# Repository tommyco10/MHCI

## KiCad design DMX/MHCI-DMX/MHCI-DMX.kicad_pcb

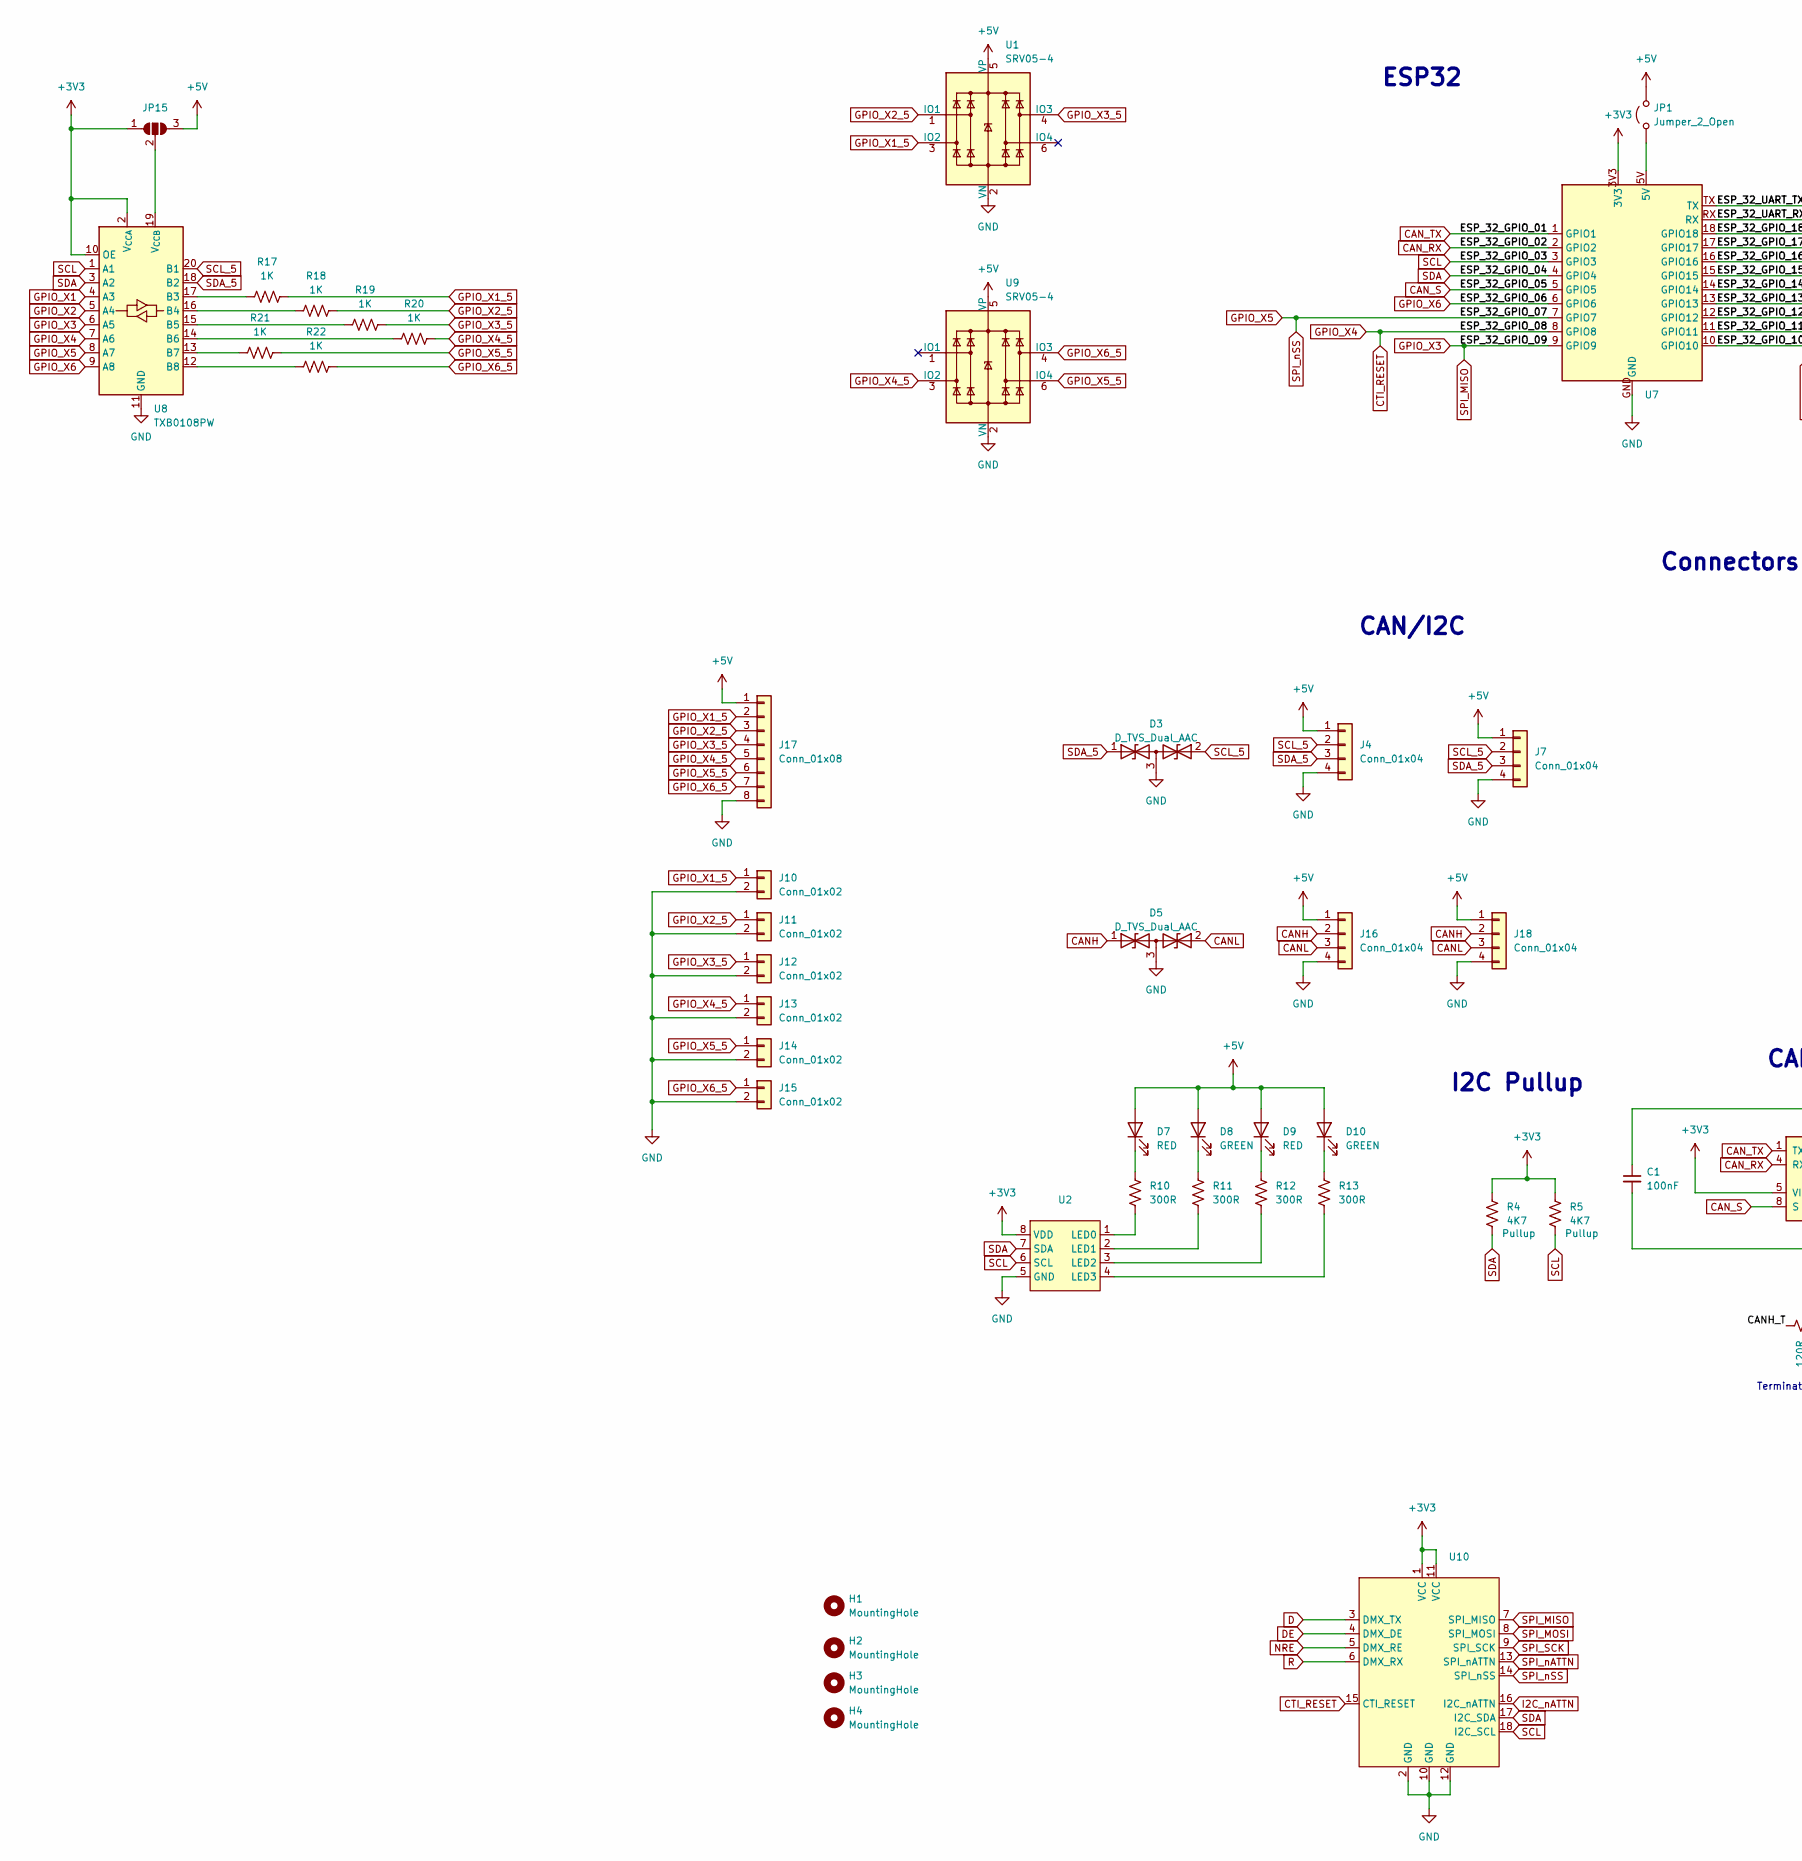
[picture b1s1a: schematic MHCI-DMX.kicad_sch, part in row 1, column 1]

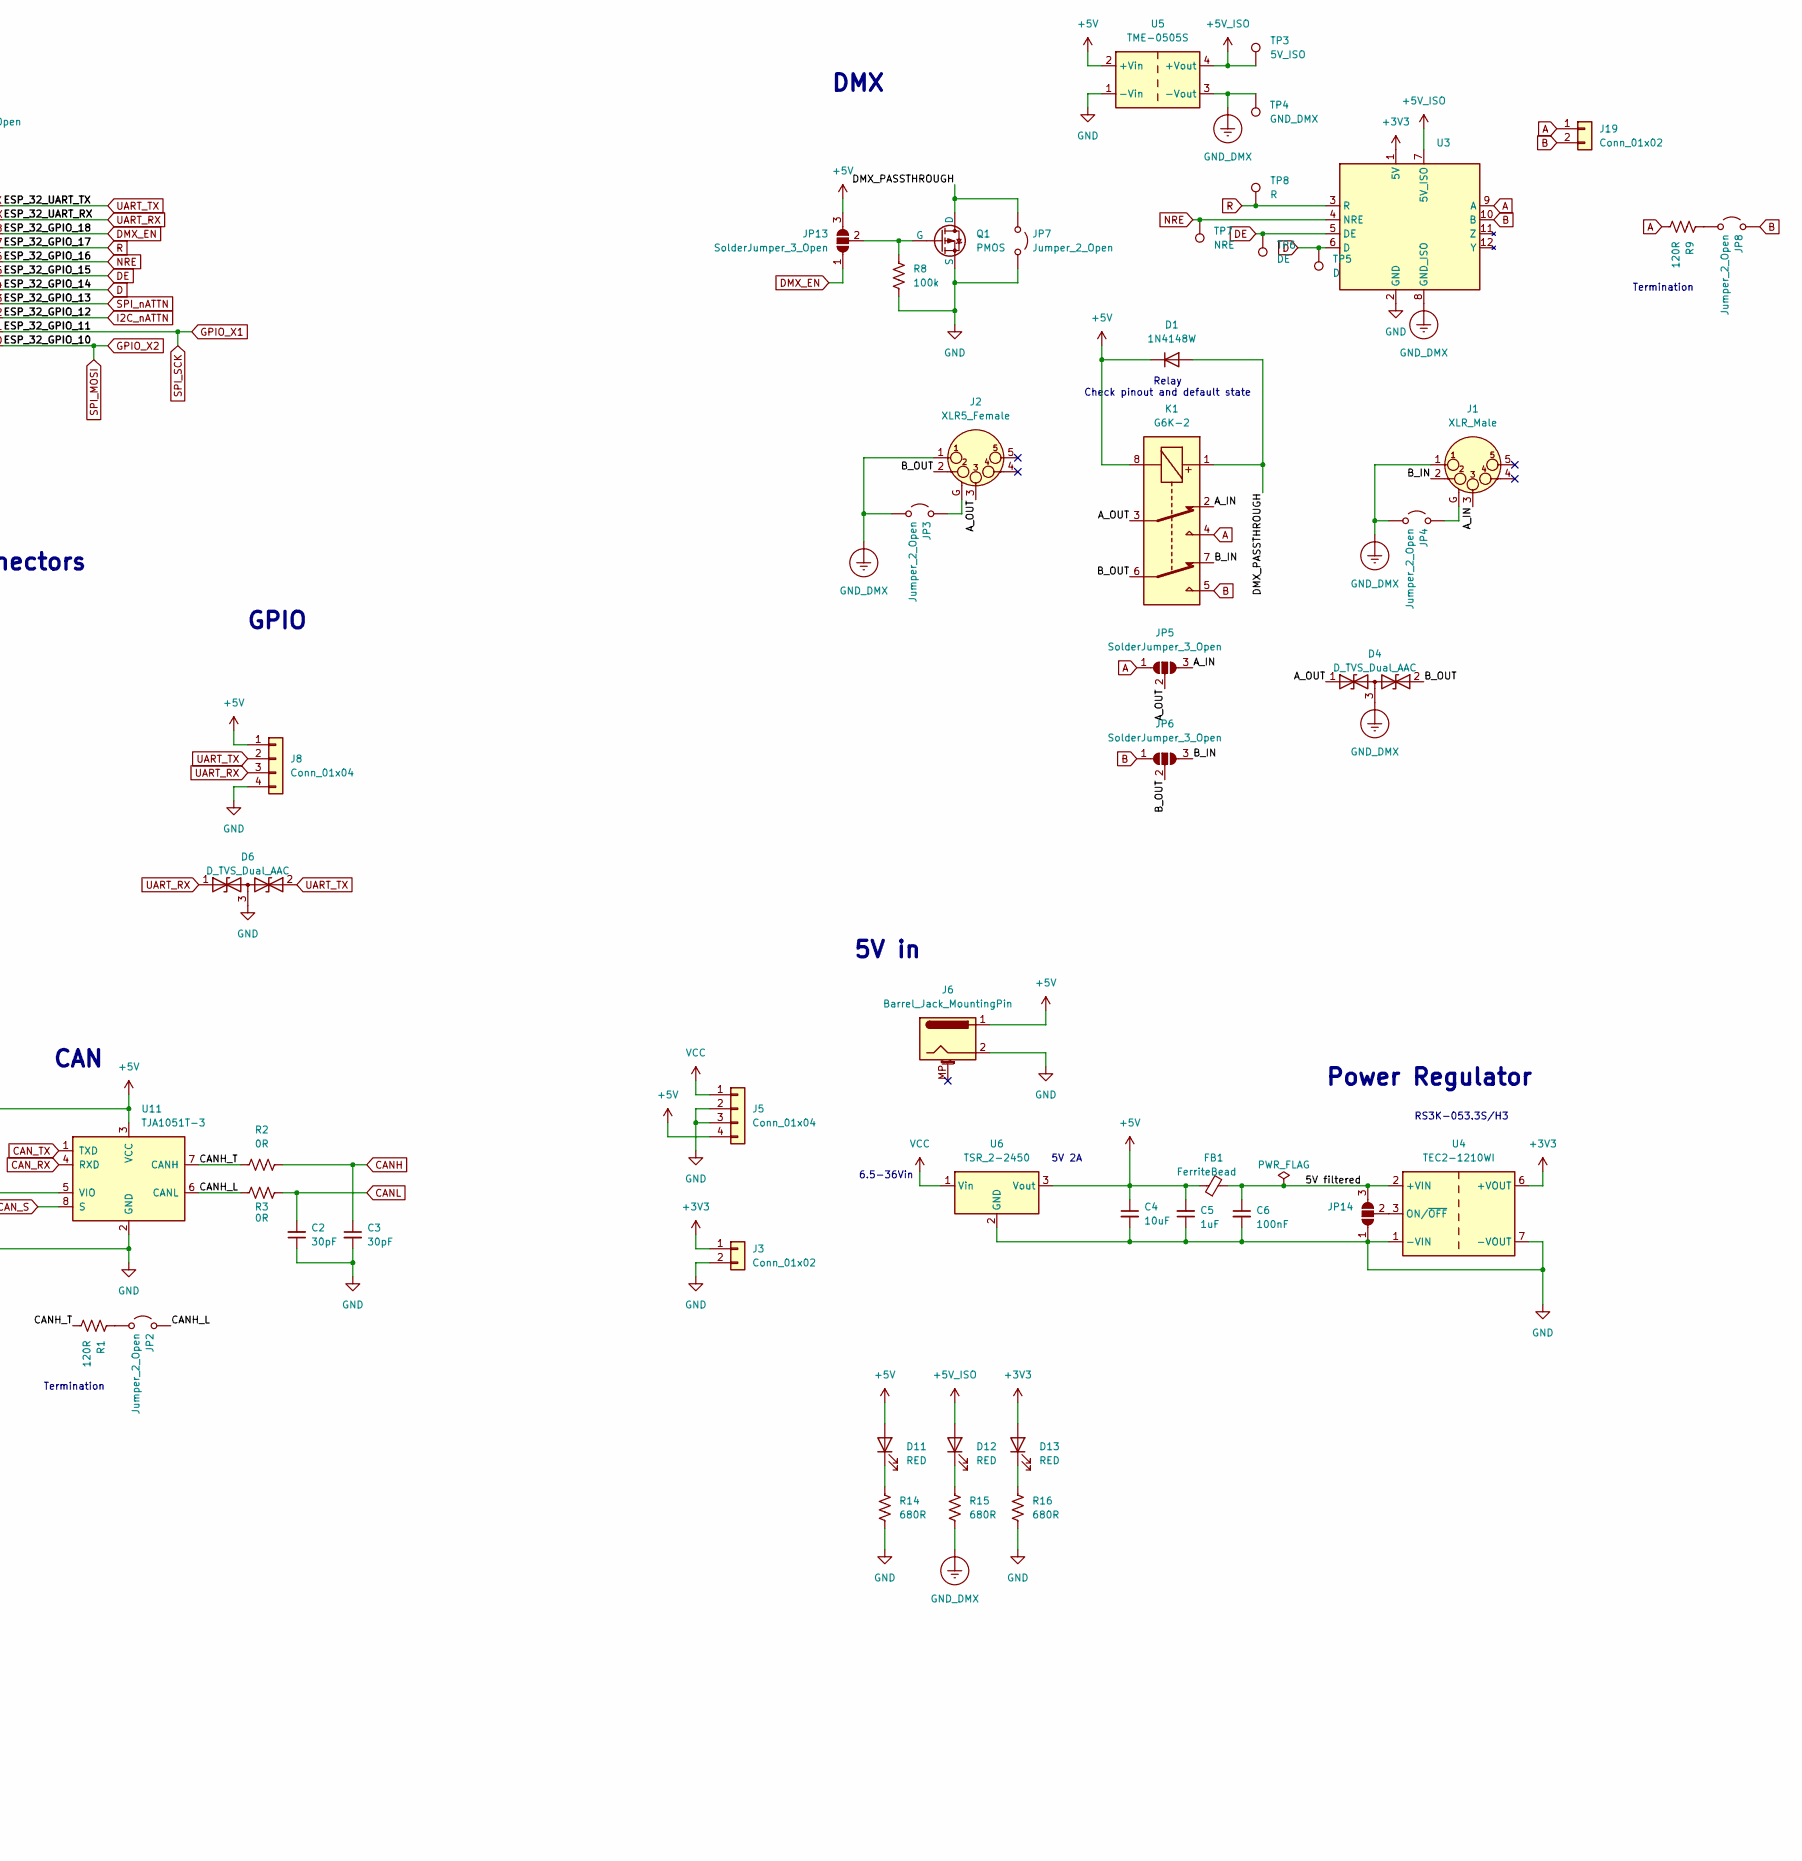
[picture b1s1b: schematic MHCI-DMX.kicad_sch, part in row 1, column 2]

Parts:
C1, C6: 100nF; C_0402_1005Metric; LCSC C1525
C2, C3: 30pF; C_0402_1005Metric; LCSC C1570
C4: 10uF; C_0603_1608Metric; LCSC C96446
C5: 1uF; C_0402_1005Metric; LCSC C52923
D1: 1N4148W; D_SOD-123; LCSC C2099
D3, D4, D5, D6: D_TVS_Dual_AAC; SOT-23; LCSC C32677
D7, D9, D11, D12, D13: RED; LED_0603_1608Metric; LCSC C2286
D8, D10: GREEN; LED_0603_1608Metric
FB1: FerriteBead; D_0805_2012Metric; LCSC C1015
H1, H2, H3, H4: MountingHole; MountingHole_3.2mm_M3
J1: XLR_Male; Jack_XLR_Neutrik_NC5MAH_LR
J2: XLR5_Female; Jack_XLR_Neutrik_NC5FAH_LR-DAE
J3, J19: Conn_01x02; PinHeader_1x02_P2.54mm_Vertical
J4, J7, J8, J16, J18: Conn_01x04; PinSocket_1x04_P2.54mm_Vertical
J5: Conn_01x04; PinHeader_1x04_P2.54mm_Vertical
J6: Barrel_Jack_MountingPin; BarrelJack_GCT_DCJ200-10-A_Horizontal
J10, J11, J12, J13, J14, J15: Conn_01x02; 2060-452-998-404 Wago
J17: Conn_01x08; PinSocket_1x08_P2.54mm_Vertical
JP1, JP2, JP3, JP4, JP7, JP8: Jumper_2_Open; SolderJumper-2_P1.3mm_Open_RoundedPad1.0x1.5mm
JP5, JP6, JP13, JP14, JP15: SolderJumper_3_Open; SolderJumper-3_P1.3mm_Open_RoundedPad1.0x1.5mm
K1: G6K-2; Relay_DPDT_Omron_G6K-2F
Q1: PMOS; SOT-23; LCSC C10487
R1, R9: 120R; R_0402_1005Metric; LCSC C25079
R2, R3: 0R; R_0402_1005Metric; LCSC C17168
R4, R5: 4K7; R_0603_1608Metric; LCSC C23162
R8: 100k; R_0603_1608Metric; LCSC C25803
R10, R11, R12, R13: 300R; R_0603_1608Metric; LCSC C23025
R14, R15, R16: 680R; R_0603_1608Metric; LCSC C23228
R17, R18, R19, R20, R21, R22: 1K; R_0603_1608Metric; LCSC C21190
TP3: 5V_ISO; TestPoint_Pad_D1.0mm
TP4: GND_DMX; TestPoint_Pad_D1.0mm
TP5: D; TestPoint_Pad_D1.0mm
TP6: DE; TestPoint_Pad_D1.0mm
TP7: NRE; TestPoint_Pad_D1.0mm
TP8: R; TestPoint_Pad_D1.0mm
U1, U9: SRV05-4; SOT-23-6; LCSC C85364
U2: TSSOP-8_3x3mm_P0.65mm; LCSC C88381
U3: ISO-DMX
U4: TEC2-1210WI; Converter_DCDC_TRACO_TMR-xxxx_THT
U5: TME-0505S; Converter_DCDC_TRACO_TME_03xxS_05xxS_12xxS_Single_THT
U6: TSR_2-2450; Converter_DCDC_TRACO_TSR-1_THT
U7: ESP-32-S3-Tiny - PTH
U8: TXB0108PW; TSSOP-20_4.4x6.5mm_P0.65mm
U10: WirelessDMX-Module
U11: TJA1051T-3; SOIC-8_3.9x4.9mm_P1.27mm; LCSC C5342108

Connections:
+3V3: D13.2 (A), J3.1, JP15.1 (A), R4.1, R5.1, U2.8 (VDD), U3.1 (5V), U4.6 (+VOUT), U7.3V3, U8.2 (V_{CCA}), U8.10 (OE), U10.1 (VCC), U10.11 (VCC), U11.5 (VIO)
+5V: C1.1, C4.1, C5.2, D1.1 (K), D7.2 (A), D8.2 (A), D9.2 (A), D10.2 (A), D11.2 (A), FB1.1, J4.1, J5.4, J6.1, J7.1, J8.1, J16.1, J17.1, J18.1, JP1.2 (B), JP13.3 (B), JP15.3 (B), K1.8, U1.5 (VP), U5.2 (+Vin), U6.3 (Vout), U9.5 (VP), U11.3 (VCC)
+5V_ISO: D12.2 (A), TP3.1, U3.7 (5V_ISO), U5.4 (+Vout)
/5V filtered: C6.1, FB1.2, JP14.3 (B), U4.2 (+VIN)
/A_IN: J1.3, JP5.3 (B), K1.2
/A_OUT: D4.1 (A1), J2.3, JP5.2 (C), K1.3
/B_IN: J1.2, JP6.3 (B), K1.7
/B_OUT: D4.2 (A2), J2.2, JP6.2 (C), K1.6
/CANH_L: JP2.2 (B), R3.1, U11.6 (CANL)
/CANH_T: R1.1, R2.2, U11.7 (CANH)
/DMX_PASSTHROUGH: D1.2 (A), JP7.1 (A), K1.1, Q1.3 (D)
A: J19.1, JP5.1 (A), K1.4, R9.1, U3.9 (A)
B: J19.2, JP6.1 (A), JP8.2 (B), K1.5, U3.10 (B)
CANH: C3.1, D5.1 (A1), J16.2, J18.2, R2.1
CANL: C2.2, D5.2 (A2), J16.3, J18.3, R3.2
CAN_RX: U7.2 (GPIO2), U11.4 (RXD)
CAN_S: U7.5 (GPIO5), U11.8 (S)
CAN_TX: U7.1 (GPIO1), U11.1 (TXD)
CTI_RESET: U7.8 (GPIO8), U8.7 (A6), U10.15 (CTI_RESET)
D: TP5.1, U3.6 (D), U7.14 (GPIO14), U10.3 (DMX_TX)
DE: TP6.1, U3.5 (DE), U7.15 (GPIO15), U10.4 (DMX_DE)
DMX_EN: JP13.1 (A), U7.18 (GPIO18)
GND: C1.2, C2.1, C3.2, C4.2, C5.1, C6.2, D3.3 (common), D5.3 (common), D6.3 (common), J3.2, J4.4, J5.2, J5.3, J6.2, J7.4, J8.4, J10.2, J11.2, J12.2, J13.2, J14.2, J15.2, J16.4, J17.8, J18.4, JP7.2 (B), JP14.1 (A), Q1.2 (S), R8.2, R14.2, R16.2, U1.2 (VN), U2.5 (GND), U3.2 (GND), U4.1 (-VIN), U4.7 (-VOUT), U5.1 (-Vin), U6.2 (GND), U7.GND, U8.11 (GND), U9.2 (VN), U10.2 (GND), U10.10 (GND), U10.12 (GND), U11.2 (GND)
GND_DMX: D4.3 (common), J1.1, J2.1, JP3.1 (A), JP4.1 (A), R15.2, TP4.1, U3.8 (GND_ISO), U5.3 (-Vout)
GPIO_X1: U7.11 (GPIO11), U8.4 (A3), U10.9 (SPI_SCK)
GPIO_X1_5: J10.1, J17.2, R17.2, U1.3 (IO2)
GPIO_X2: U7.10 (GPIO10), U8.5 (A4), U10.8 (SPI_MOSI)
GPIO_X2_5: J11.1, J17.3, R18.2, U1.1 (IO1)
GPIO_X3: U7.9 (GPIO9), U8.6 (A5), U10.7 (SPI_MISO)
GPIO_X3_5: J12.1, J17.4, R19.2, U1.4 (IO3)
GPIO_X4_5: J13.1, J17.5, R20.2, U9.3 (IO2)
GPIO_X5: U7.7 (GPIO7), U8.8 (A7), U10.14 (SPI_nSS)
GPIO_X5_5: J14.1, J17.6, R21.2, U9.6 (IO4)
GPIO_X6: U7.6 (GPIO6), U8.9 (A8)
GPIO_X6_5: J15.1, J17.7, R22.2, U9.4 (IO3)
I2C_nATTN: U7.12 (GPIO12), U10.16 (I2C_nATTN)
NRE: TP7.1, U3.4 (NRE), U7.16 (GPIO16), U10.5 (DMX_RE)
unnamed: D7.1 (K), R10.1
unnamed: D8.1 (K), R11.1
unnamed: D9.1 (K), R12.1
unnamed: D10.1 (K), R13.1
unnamed: D11.1 (K), R14.1
unnamed: D12.1 (K), R15.1
unnamed: D13.1 (K), R16.1
unnamed: JP1.1 (A), U7.5V
unnamed: JP2.1 (A), R1.2
unnamed: J2.G, JP3.2 (B)
unnamed: J1.G, JP4.2 (B)
unnamed: JP8.1 (A), R9.2
unnamed: JP13.2 (C), Q1.1 (G), R8.1
unnamed: JP14.2 (C), U4.3 (ON/~OFF)
unnamed: JP15.2 (C), U8.19 (V_{CCB})
unnamed: R10.2, U2.1 (LED0)
unnamed: R11.2, U2.2 (LED1)
unnamed: R12.2, U2.3 (LED2)
unnamed: R13.2, U2.4 (LED3)
unnamed: R17.1, U8.17 (B3)
unnamed: R18.1, U8.16 (B4)
unnamed: R19.1, U8.15 (B5)
unnamed: R20.1, U8.14 (B6)
unnamed: R21.1, U8.13 (B7)
unnamed: R22.1, U8.12 (B8)
R: TP8.1, U3.3 (R), U7.17 (GPIO17), U10.6 (DMX_RX)
SCL: R5.2, U2.6 (SCL), U7.3 (GPIO3), U8.1 (A1), U10.18 (I2C_SCL)
SCL_5: D3.2 (A2), J4.2, J7.2, U8.20 (B1)
SDA: R4.2, U2.7 (SDA), U7.4 (GPIO4), U8.3 (A2), U10.17 (I2C_SDA)
SDA_5: D3.1 (A1), J4.3, J7.3, U8.18 (B2)
SPI_nATTN: U7.13 (GPIO13), U10.13 (SPI_nATTN)
UART_RX: D6.1 (A1), J8.3, U7.RX
UART_TX: D6.2 (A2), J8.2, U7.TX
VCC: J5.1, U6.1 (Vin)

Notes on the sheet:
Connectors
5V 2A
CAN
DMX
Termination
RS3K-053.3S/H3
5V in
Relay Check pinout and default state
ESP32
CAN/I2C
I2C Pullup
GPIO
Power Regulator
6.5-36Vin

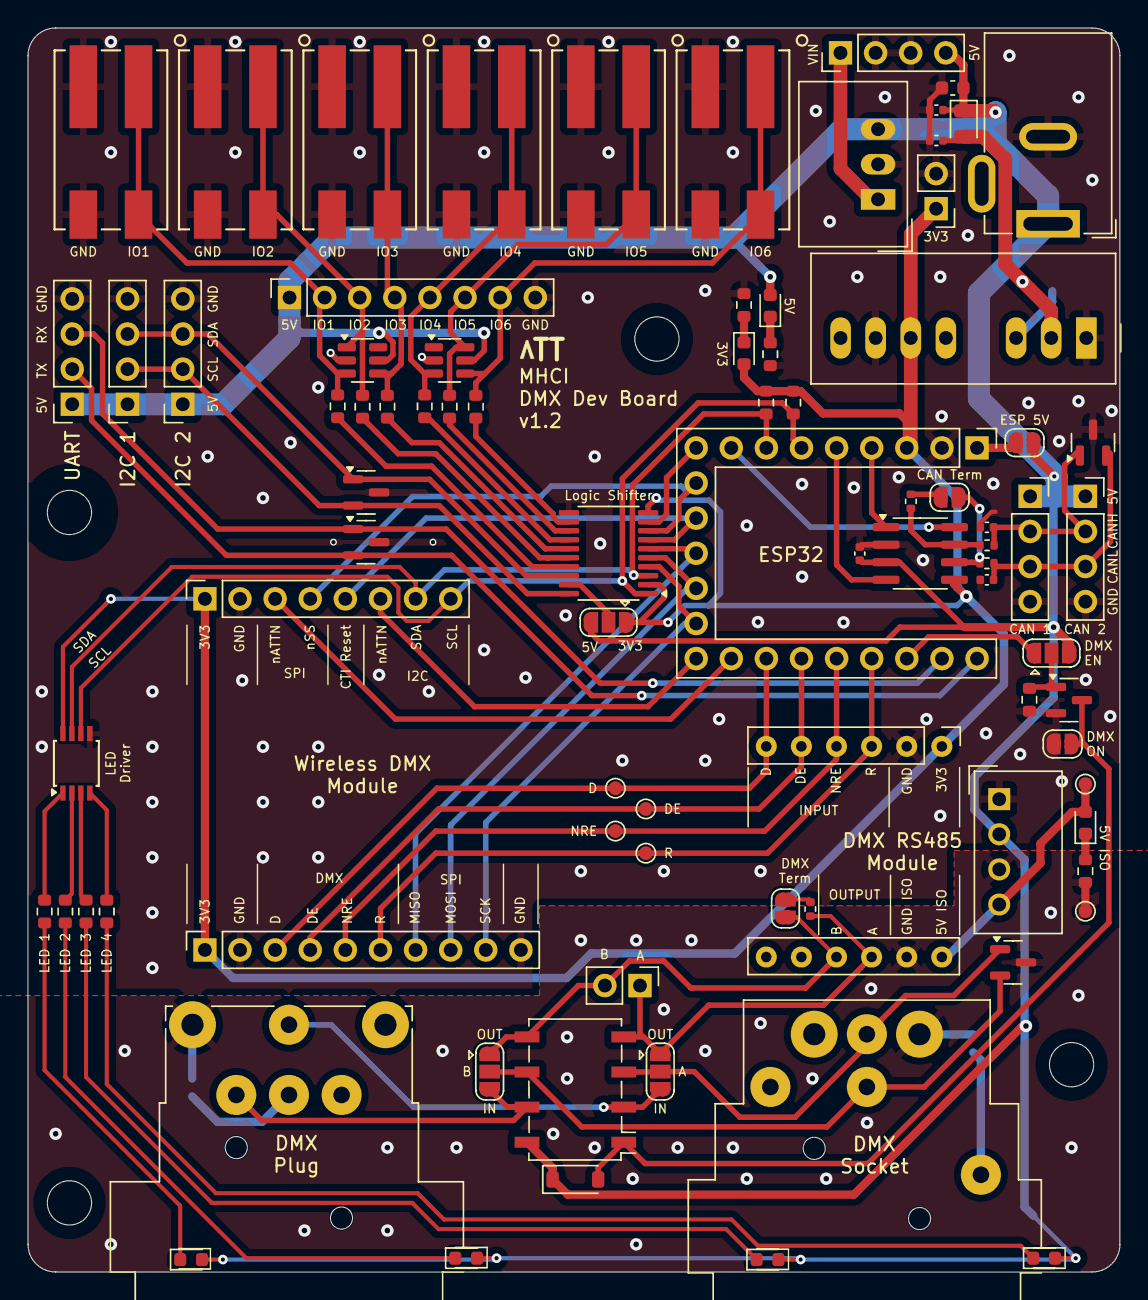
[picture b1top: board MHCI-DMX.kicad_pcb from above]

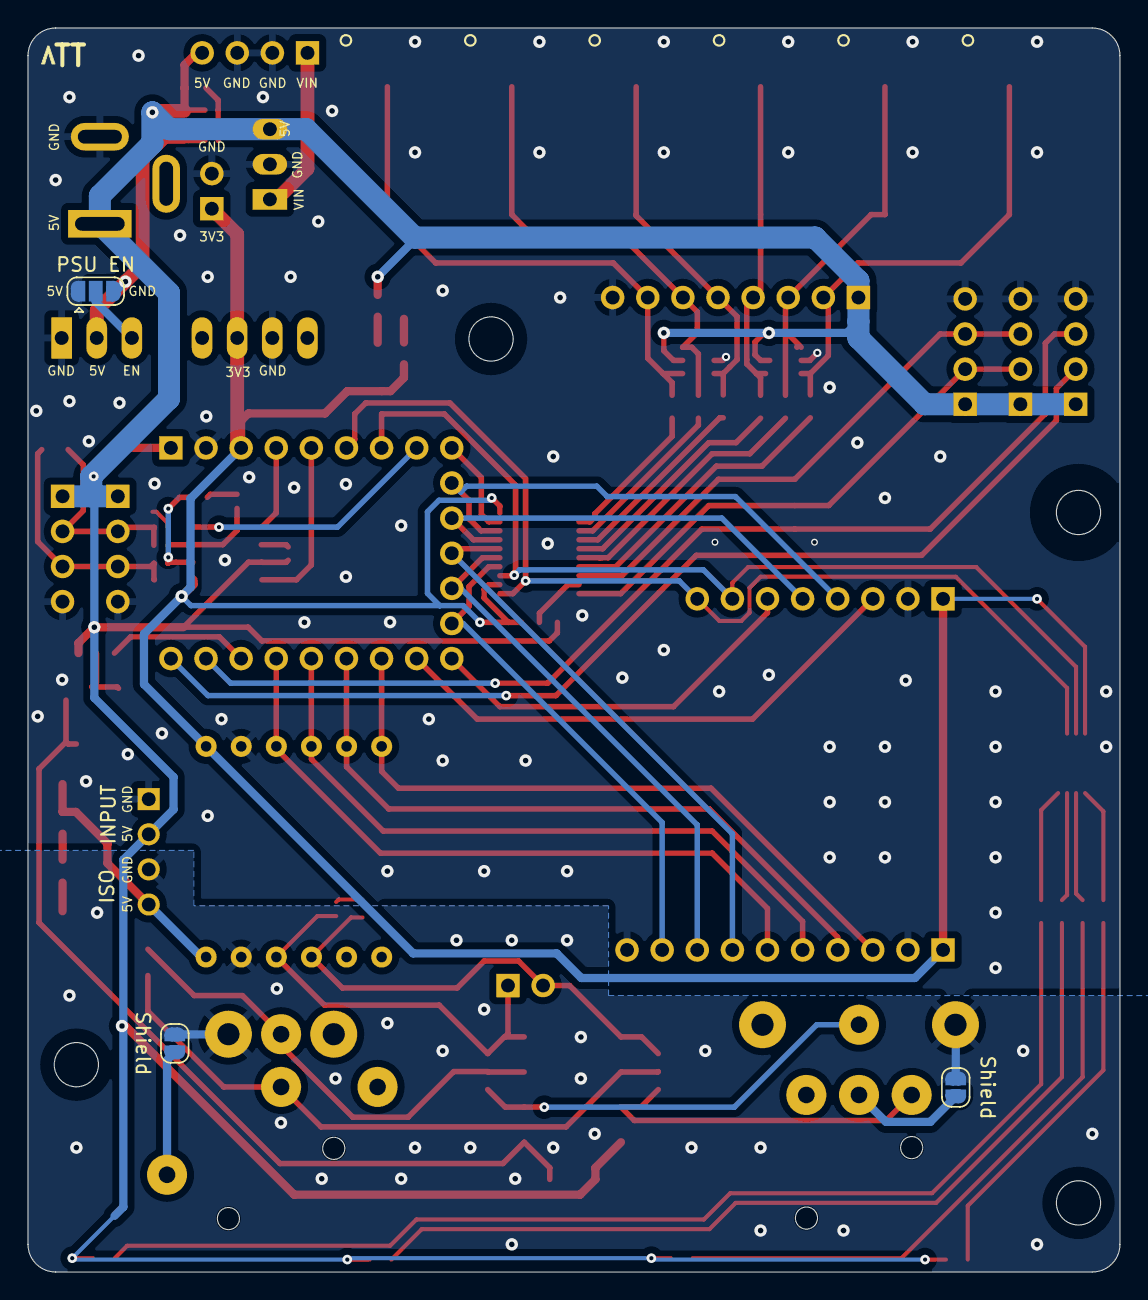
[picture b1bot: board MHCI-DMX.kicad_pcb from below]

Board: 2 copper layers, 79.0 x 90.0 mm, 91 parts (3 on the bottom side), 71 nets.

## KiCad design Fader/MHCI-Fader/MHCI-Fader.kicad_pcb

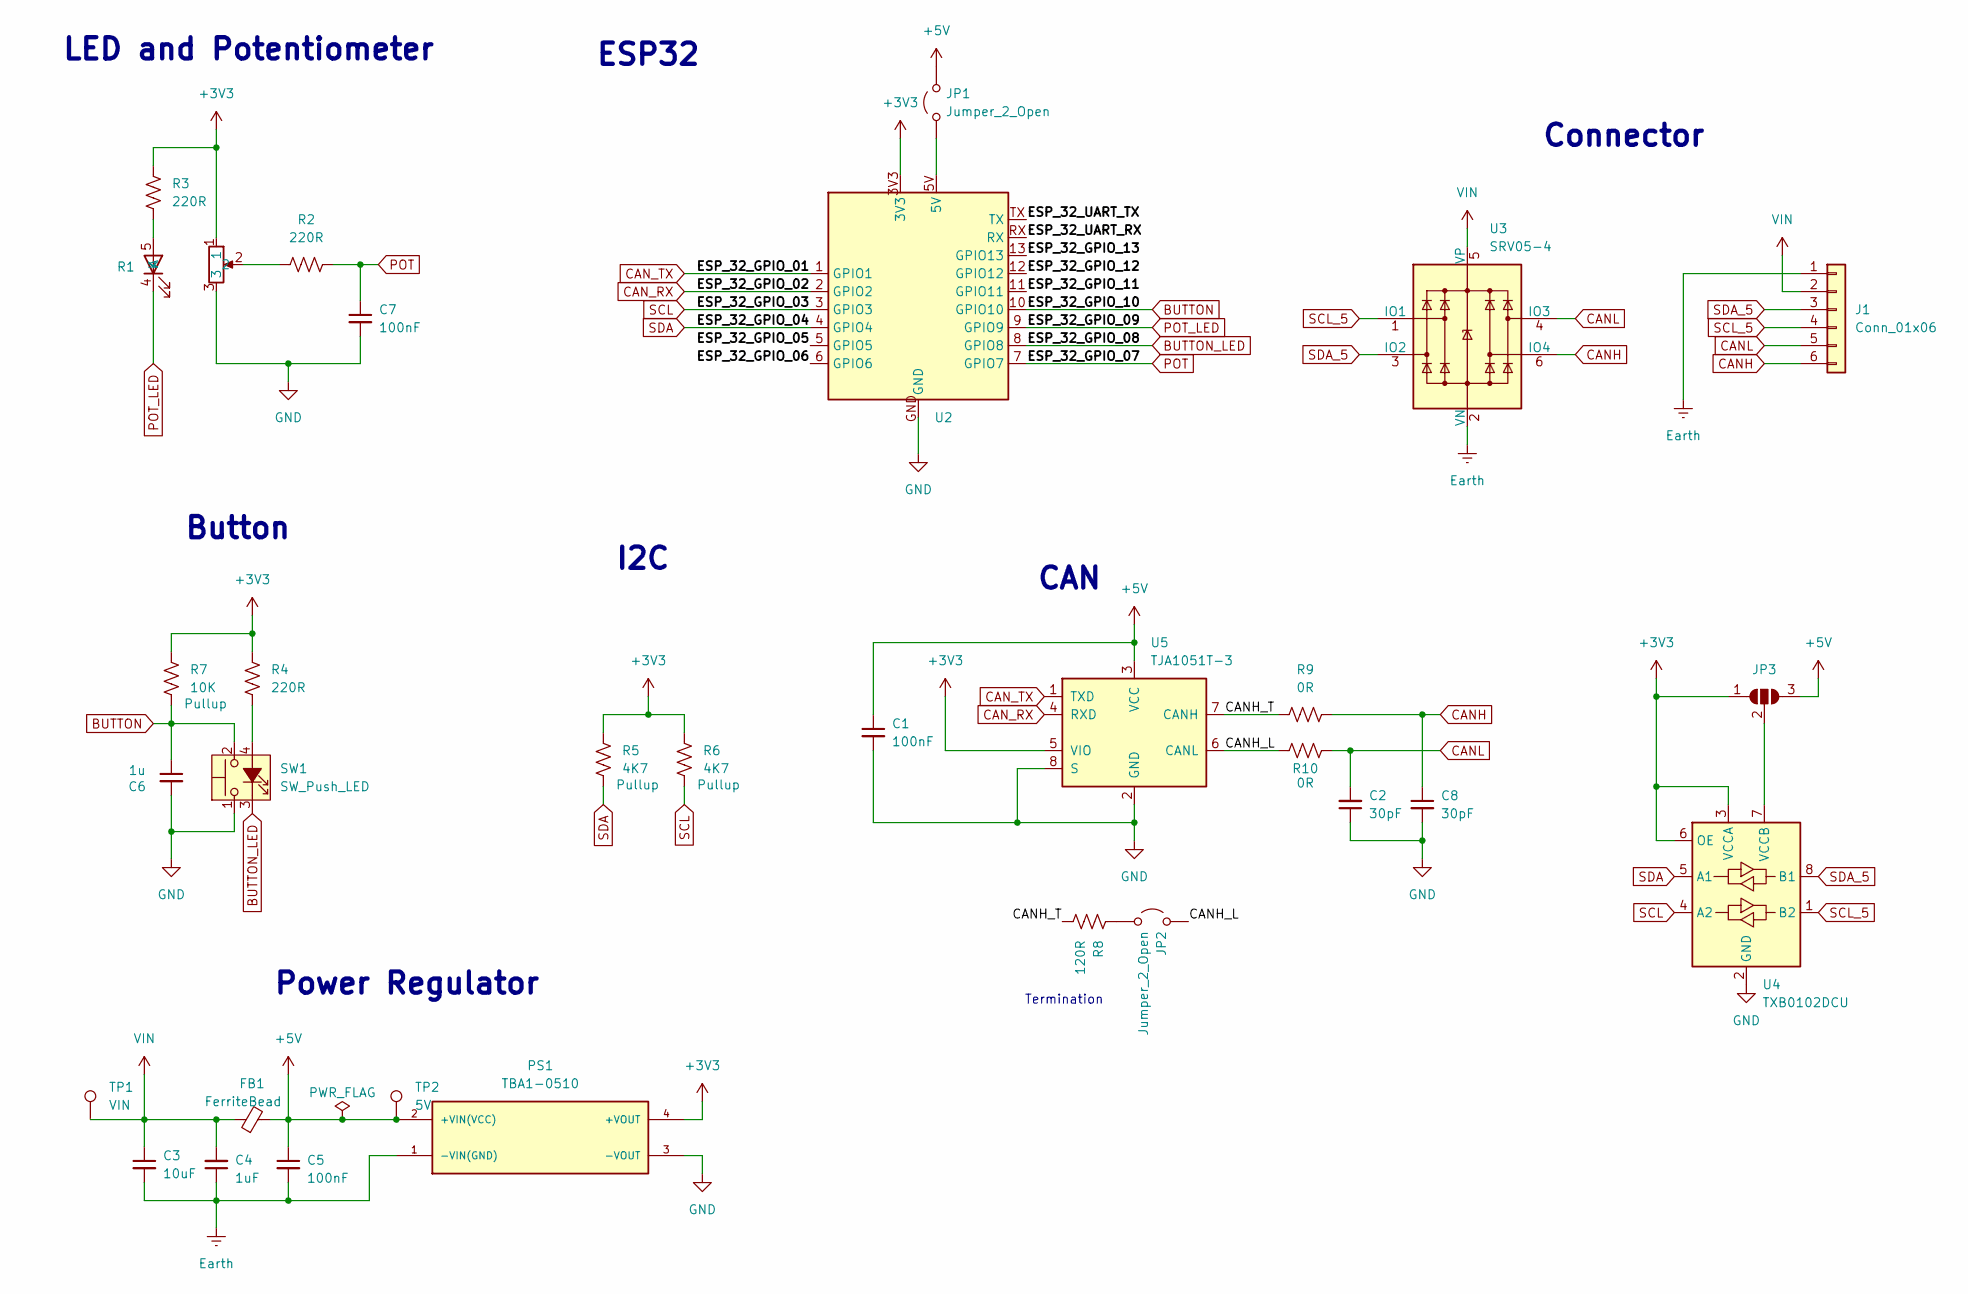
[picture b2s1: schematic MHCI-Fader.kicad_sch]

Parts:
C1, C5, C7: 100nF; C_0402_1005Metric; LCSC C1525
C2, C8: 30pF; C_0402_1005Metric; LCSC C1570
C3: 10uF; C_0603_1608Metric; LCSC C96446
C4: 1uF; C_0402_1005Metric; LCSC C52923
C6: 1u; C_0402_1005Metric; LCSC C52923
FB1: FerriteBead; D_0805_2012Metric; LCSC C1015
J1: Conn_01x06; PinHeader_1x06_P2.54mm_Vertical
JP1, JP2: Jumper_2_Open; SolderJumper-2_P1.3mm_Open_RoundedPad1.0x1.5mm
JP3: SolderJumper_3_Open; SolderJumper-3_P1.3mm_Open_RoundedPad1.0x1.5mm
PS1: TBA1-0510; CONV_TBA1-0510; PARTREV April 19, 2021
R1: Linear Potentiometer LED 60mm
R2, R3, R4: 220R; R_0402_1005Metric; LCSC C25091
R5, R6: 4K7; R_0603_1608Metric; LCSC C23162
R7: 10K; R_0402_1005Metric; LCSC C25744
R8: 120R; R_0402_1005Metric; LCSC C25079
R9, R10: 0R; R_0402_1005Metric; LCSC C17168
SW1: SW_Push_LED; SP86N_AB Switch
TP1: VIN; TestPoint_Pad_D1.0mm
TP2: 5V; TestPoint_Pad_D1.0mm
U2: ESP-32-S3-Zero - SMD
U3: SRV05-4; SOT-23-6; LCSC C85364
U4: TXB0102DCU; VSSOP-8_2.3x2mm_P0.5mm; LCSC C60709
U5: TJA1051T-3; SOIC-8_3.9x4.9mm_P1.27mm; LCSC C5342108

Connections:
+3V3: JP3.1 (A), PS1.4 (+VOUT), R1.1, R3.2, R4.2, R5.1, R6.1, R7.1, U2.3V3, U4.3 (VCCA), U4.6 (OE), U5.5 (VIO)
+5V: C1.1, C5.1, FB1.2, JP1.2 (B), JP3.3 (B), PS1.2 (+VIN(VCC)), TP2.1, U5.3 (VCC)
/CANH_L: JP2.2 (B), R10.1, U5.6 (CANL)
/CANH_T: R8.1, R9.2, U5.7 (CANH)
/ESP_32_GPIO_05: U2.5 (GPIO5)
/ESP_32_GPIO_06: U2.6 (GPIO6)
/ESP_32_GPIO_11: U2.11 (GPIO11)
/ESP_32_GPIO_12: U2.12 (GPIO12)
/ESP_32_GPIO_13: U2.13 (GPIO13)
/ESP_32_UART_RX: U2.RX
/ESP_32_UART_TX: U2.TX
BUTTON: C6.1, R7.2, SW1.2, U2.10 (GPIO10)
BUTTON_LED: SW1.3 (K), U2.8 (GPIO8)
CANH: C8.1, J1.6, R9.1, U3.6 (IO4)
CANL: C2.2, J1.5, R10.2, U3.4 (IO3)
CAN_RX: U2.2 (GPIO2), U5.4 (RXD)
CAN_TX: U2.1 (GPIO1), U5.1 (TXD)
Earth: C3.2, C4.1, C5.2, J1.1, PS1.1 (-VIN(GND)), U3.2 (VN)
GND: C1.2, C2.1, C6.2, C7.2, C8.2, PS1.3 (-VOUT), R1.3, SW1.1, U2.GND, U4.2 (GND), U5.2 (GND), U5.8 (S)
unnamed: JP1.1 (A), U2.5V
unnamed: JP2.1 (A), R8.2
unnamed: JP3.2 (C), U4.7 (VCCB)
unnamed: R1.5 (A), R3.1
unnamed: R1.2, R2.2
unnamed: R4.1, SW1.4 (A)
POT: C7.1, R2.1, U2.7 (GPIO7)
POT_LED: R1.4 (K), U2.9 (GPIO9)
SCL: R6.2, U2.3 (GPIO3), U4.4 (A2)
SCL_5: J1.4, U3.1 (IO1), U4.1 (B2)
SDA: R5.2, U2.4 (GPIO4), U4.5 (A1)
SDA_5: J1.3, U3.3 (IO2), U4.8 (B1)
VIN: C3.1, C4.2, FB1.1, J1.2, TP1.1, U3.5 (VP)

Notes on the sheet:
Connector
Termination
I2C
CAN
Power Regulator
ESP32
Button
LED and Potentiometer

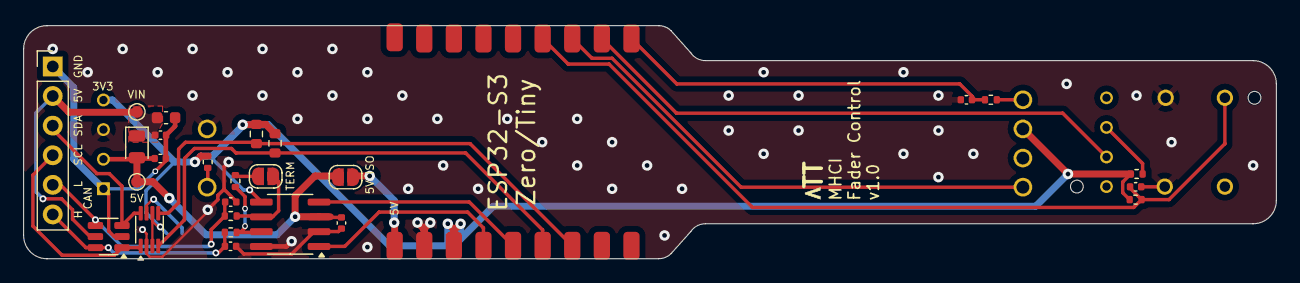
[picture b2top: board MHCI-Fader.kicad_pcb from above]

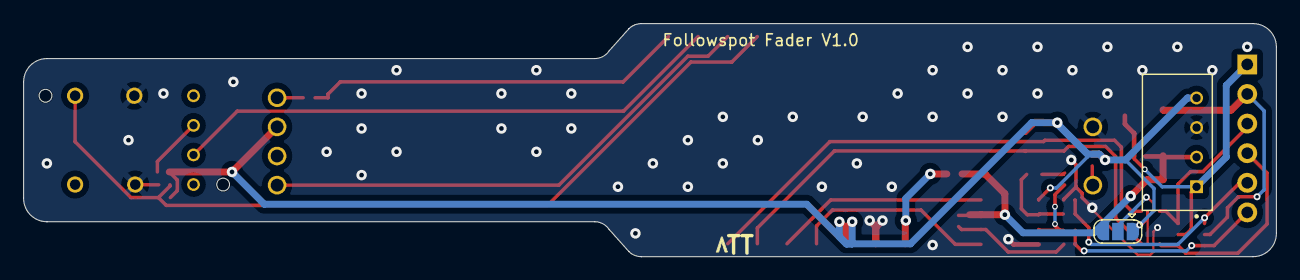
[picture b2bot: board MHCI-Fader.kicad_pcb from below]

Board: 2 copper layers, 107.5 x 20.0 mm, 31 parts (4 on the bottom side), 25 nets.

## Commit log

2024-12-19 Fader Footprint
2024-12-24 Add all Waveshare footprints
2024-12-24 Initial fader schematic
2024-12-24 Fix button schematic
2024-12-24 Fader layout complete
2024-12-27 Adjusted fader layout to compact arrangement
2024-12-27 Production files
2024-12-27 Fader silkscreen
2024-12-27 Fader silkscreen ATT
2024-12-27 Initial DMX Schematic
2024-12-28 DMX Schematic complete, and initial Layout
2025-01-03 CRMX-TIMO 3D file
2025-01-03 Add CRMX and MV footprints to HMCI Library
2025-01-03 MHCI Fader - Add logic level converter and re-route traces
2025-01-03 MHCI DMX - Finalise schematic and initial layout routing
2025-01-04 Adding LEDs to DMX plug and socket.
2025-01-05 Logos and description
2025-01-05 MHCI Production Read
2025-01-05 v1.0 Production Files
    Small ground connection fixed.
2025-01-23 Adding the MHCI-DMX board v1.0 as a separate footprint
2025-01-24 Adding 3d model files
2025-01-24 Adding the MHCI-A6211 board v1.0 as a separate footprint
2025-01-27 A6211 and MHCI DMX Board 3D files
2025-01-27 Initial DMX src files
2025-01-27 Initial fader src files
2025-01-28 Update DMX board with v1.1 updates
2025-01-28 MHCI-DMX v1.1 hardware
2025-01-29 Attempting to fix PWM
2025-01-30 Fixing PWM duty cycles
2025-01-30 MHCI DMX v1.2 production files
2025-04-11 Adding pogo connector
2025-05-09 MHCI-DMX - Testing screen and DMX output
2025-06-05 Port od LED2 main for environment testing
2025-06-05 Port of MHCILed2 for environment testing
2025-06-05 commenting out OTA
2025-06-05 TCO platformio ini with correct pins for ESP32 Wroom32E
2025-06-07 correct ini for compliation on wroom32
2025-06-07 sender test code
2025-06-07 dmx i2c reciever test
2025-06-07 updated sender code
2025-06-07 new reciever code
2025-06-07 new i2c code
2025-06-07 working serial monitr but not led
2025-06-07 working no scurve
2025-06-07 working but what about dmx universe? only 32 values read

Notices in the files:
parts and their libraries:
Copyright 2016 Accelerated Designs. All rights reserved.
